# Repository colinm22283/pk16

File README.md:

# PK16

## Requirements
Must have [customasm](https://github.com/hlorenzi/customasm) installed and in your path

## Opcodes
### Format
```
0<OSLCT>-<SS><DD>
1<DD><O>-<IMMVAL>

OSLCT/O: operation select
SS:      source register
DD:      destination register
IMMVAL:  immediate value
```

### List
| Instruction | Description                        | Opcode              |
|-------------|------------------------------------|---------------------|
| `mov`       | DD = SS                            | `00000000-<SS><DD>` |
| `add.r`     | DD = DD + SS                       | `00000001-<SS><DD>` |
| `sub.r`     | DD = DD - SS                       | `00000010-<SS><DD>` |
| `and`       | DD = DD & SS                       | `00000011-<SS><DD>` |
| `or`        | DD = DD \| SS                      | `00000100-<SS><DD>` |
| `xor`       | DD = DD ^ SS                       | `00000101-<SS><DD>` |
| `shl`       | DD = DD << SS                      | `00000110-<SS><DD>` |
| `shr`       | DD = DD >> SS                      | `00000111-<SS><DD>` |
| `jmp.l`     | Jump to DD                         | `00010000-<SS><DD>` |
| `br.l`      | Jump if true to DD                 | `00010001-<SS><DD>` |
| `jmp.r`     | Relative jump by DD * 2            | `00010010-<SS><DD>` |
| `br.r`      | Relative jump if true by DD * 2    | `00010011-<SS><DD>` |
| `ce`        | Compare equal                      | `00010100-<SS><DD>` |
| `cl`        | Compare less than                  | `00010111-<SS><DD>` |
| `cle`       | Compare less than or equal         | `00011000-<SS><DD>` |
| `ld.l`      | DD lower = mem[SS]                 | `00100000-<SS><DD>` |
| `ld.u`      | DD upper = mem[SS]                 | `00100010-<SS><DD>` |
| `st.l`      | mem[DD] = SS lower                 | `00100011-<SS><DD>` |
| `st.u`      | mem[DD] = SS upper                 | `00100100-<SS><DD>` |
| `pop.l`     | DD lower = stack[stp]              | `00100101-<SS><DD>` |
| `pop.u`     | DD upper = stack[stp]              | `00100110-<SS><DD>` |
| `psh.l`     | stack[stp] = SS lower              | `00100111-<SS><DD>` |
| `psh.u`     | stack[stp] = SS upper              | `00101000-<SS><DD>` |
| `swi`       | Software interrupt                 | `00110000-<SS><DD>` |
| `irt`       | Interrupt return                   | `00110001-<SS><DD>` |
| `imm.l`     | DD lower = IMMVAL                  | `1<DD>000-<IMMVAL>` |
| `imm.u`     | DD upper = IMMVAL                  | `1<DD>001-<IMMVAL>` |
| `add.i`     | DD += IMMVAL                       | `1<DD>010-<IMMVAL>` |
| `sub.i`     | DD -= IMMVAL                       | `1<DD>011-<IMMVAL>` |
| `psh.i`     | stack[stp] = IMMVAL                | `1<DD>100-<IMMVAL>` |
| `jmp.ri`    | Relative jump by IMMVAL*2          | `1<DD>101-<IMMVAL>` |
| `br.ri`     | Relative jump if true by IMMVAL*2  | `1<DD>110-<IMMVAL>` |

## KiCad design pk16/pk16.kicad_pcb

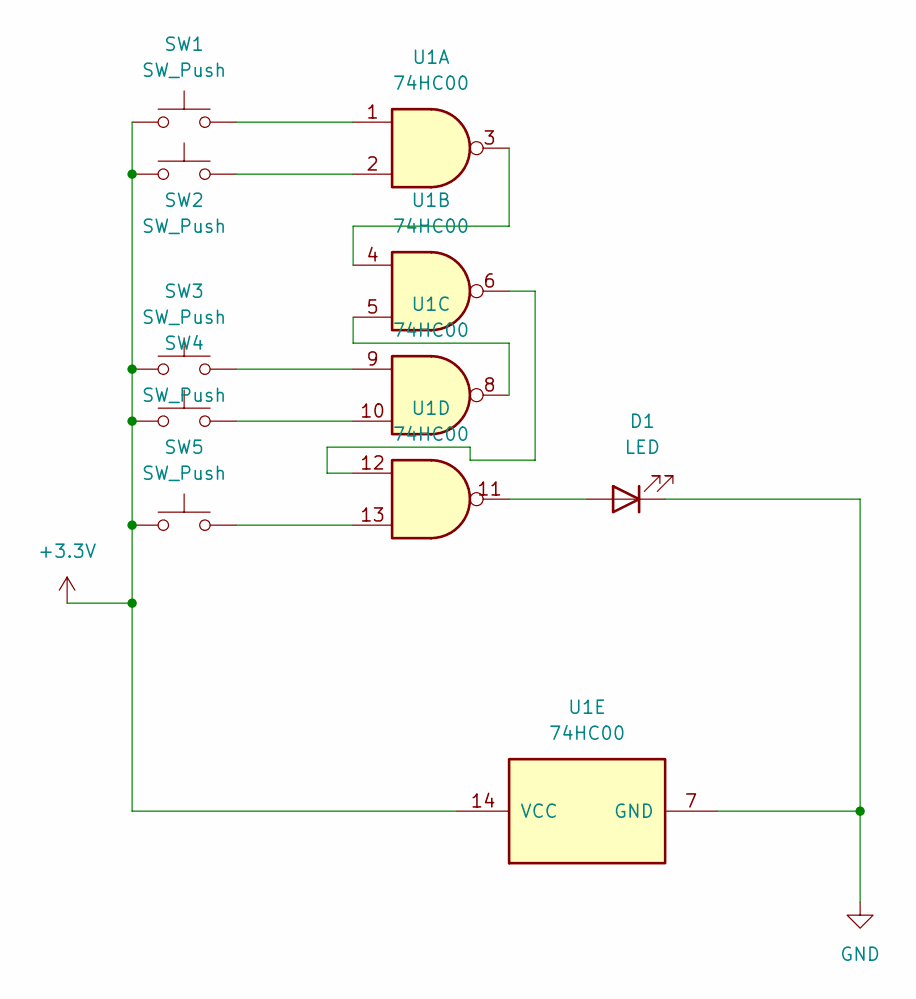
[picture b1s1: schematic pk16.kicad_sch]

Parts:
D1: LED; LED_D3.0mm
SW1, SW2, SW3, SW4, SW5: SW_Push; SW_PUSH_6mm
U1: 74HC00; DIP-14_W7.62mm_Socket

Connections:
+3.3V: SW1.1, SW2.1, SW3.1, SW4.1, SW5.1, U1.14 (VCC)
GND: D1.1 (K), U1.7 (GND)
unnamed: D1.2 (A), U1.11
unnamed: SW1.2, U1.1
unnamed: SW2.2, U1.2
unnamed: SW3.2, U1.9
unnamed: SW4.2, U1.10
unnamed: SW5.2, U1.13
unnamed: U1.3, U1.4
unnamed: U1.5, U1.8
unnamed: U1.6, U1.12

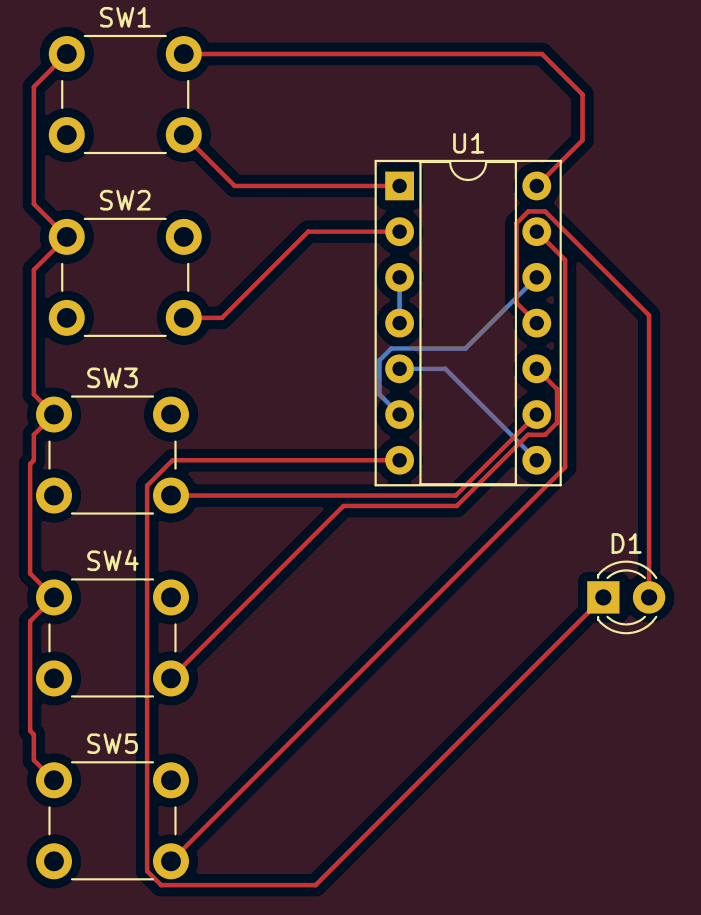
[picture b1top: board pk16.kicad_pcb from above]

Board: 2 copper layers, 7 parts (0 on the bottom side), 11 nets.

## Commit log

2023-01-19 Added Logisim libs
2023-01-19 Added more Logisim libs
2023-01-23 Opcode Reader Complete
2023-01-27 - Added more opcode - Added a bus spec
2023-01-27 Added more opcodes
2023-03-07 Made a blinky program
2023-03-09 Opcodes working!
2023-03-21 AAAAA
2023-03-22 Changed opcode to include microcode
2023-03-27 Worked on library stuff
2023-03-27 Peripherals changed
2023-03-27 Stuff
2023-03-27 Working on stack module
2023-03-27 Worked on stack some more
2023-03-29 Backed up circuit
2023-03-29 Working on the bus
2023-03-29 More bussin
2023-03-30 Even more bussin
2023-04-03 Worked on a keyboard library
2023-04-03 Did a little circuit work
2023-04-03 Made a editable board program
2023-04-07 More library stuff
2023-04-07 More circuit work
2023-04-09 Circuit
2023-04-09 MOVING AND ADDING WORKS
    Also immediate values
2023-04-09 Fibonacci
2023-04-10 CUBIC PROGRAM!!!!!!!!!!!!!!!!!!!!!!!!!!!!
2023-04-10 LOGICAL INSTRUCTIONS COMPLETE (cool)
2023-04-10 Issues jumping to ram locations
2023-04-10 Able to jump to ram now
2023-04-11 Stack controller needs some work
2023-04-14 Added a stack test program
2023-04-14 ITS COMPLETE!!!
    (almost...)
2023-04-17 Malloc is working???
2023-04-17 Heap malloc and free working
2023-04-17 Working on a possible display driver
2023-04-18 Started work on peripheral read capabilities
2023-04-18 Bad factorial thing About to start on peripherals
2023-04-19 interrupt stuff
2023-04-20 Did some peripheral work
2023-04-20 started work on the flags register
2023-04-20 did more peripheraling
2023-04-20 Working on interrupts
2023-04-21 Stupid flags register don't work
2023-04-27 Finished the carry system
2023-04-28 I broke the ram write stuff
2023-05-07 More interrupt!?!?!?!??!?!?!111
2023-05-09 INTERRUPTESESESE!!!@#@#@!#@#
2023-05-09 Have some more interrupt work to do :(
2023-05-09 Interrupt controller works!!!
2023-05-12 Starting work on the gpu and interrupt controller
2023-05-21 Need to make comparison registers save on interrupt
2023-06-03 Added many thing ig
2023-06-23 Compiler!
2023-06-23 CRUMB stuff
2023-07-04 Compiler stuff
2023-08-30 Compiler works
2023-11-02 More jorus
2023-11-21 Many things
2024-01-20 Modified entry
2024-05-08 CMake edits
2024-05-08 Remove everything
2024-05-09 Initial
2024-06-24 Starting work on v2
2024-09-09 Got a basic instruction set started
2024-09-16 Instruction set is pretty much complete
2024-10-15 Removed dead compiler directory
